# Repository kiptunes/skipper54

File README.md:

# tandem56
A partially-wired split keyboard that runs on one bluetooth-enabled microcontroller, one battery, and ZMK.

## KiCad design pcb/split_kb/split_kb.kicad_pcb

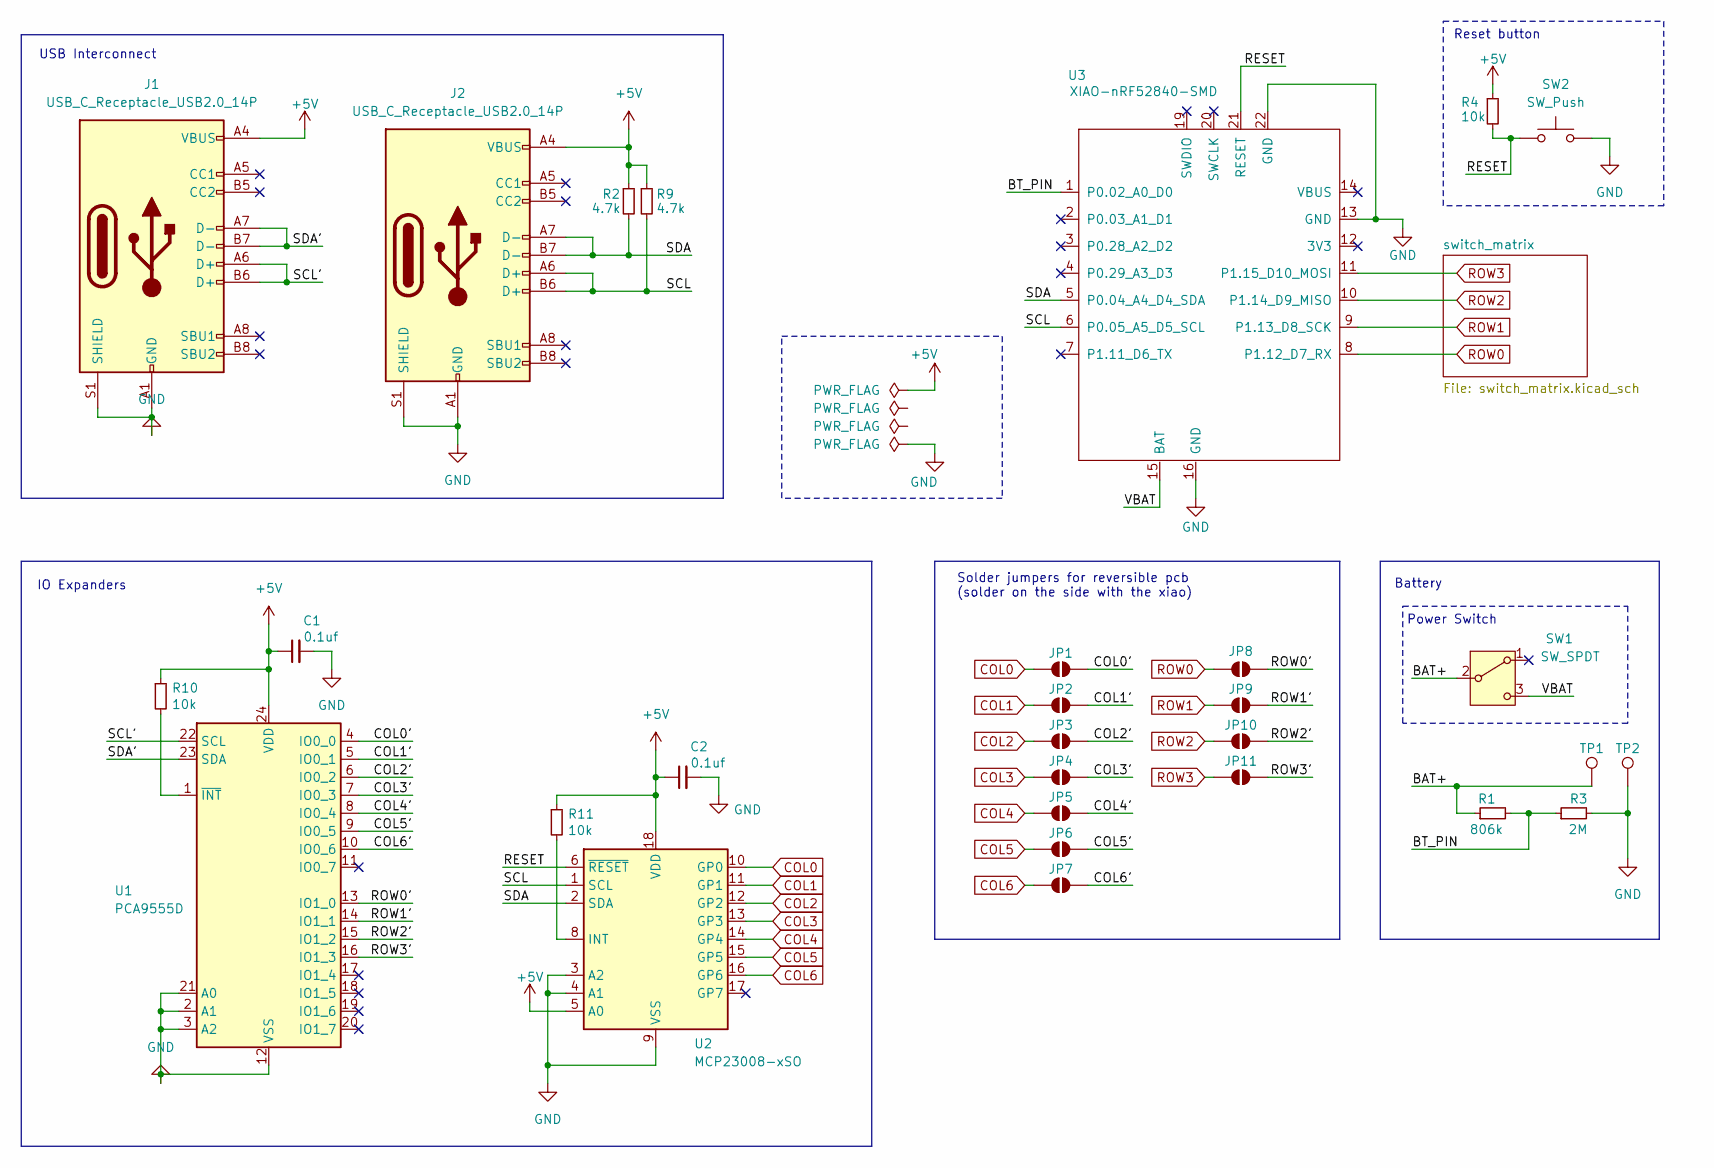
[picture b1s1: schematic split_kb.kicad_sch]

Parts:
C1, C2: 0.1uf; C_0805_2012Metric
J1, J2: USB_C_Receptacle_USB2.0_14P; USB_C_Receptacle_GCT_USB4105-xx-A_16P_TopMnt_Horizontal
JP1, JP2, JP3, JP4, JP5, JP6, JP7, JP8, JP9, JP10, JP11: SolderJumper_2_Open; SolderJumper-2_P1.3mm_Open_TrianglePad1.0x1.5mm
R1: 806k; R_0805_2012Metric
R2, R9: 4.7k; R_0805_2012Metric
R3: 2M; R_0805_2012Metric
R4, R10, R11: 10k; R_0805_2012Metric
SW1: SW_SPDT; SW_SPDT_CK_JS102011SAQN
SW2: SW_Push; SW_Tactile_SPST_Angled_PTS645Vx31-2LFS
TP1, TP2: TestPoint; TestPoint_Pad_D2.0mm
U1: PCA9555D; SSOP-24_5.3x8.2mm_P0.65mm
U2: MCP23008-xSO; SOIC-18W_7.5x11.6mm_P1.27mm
U3: XIAO-nRF52840-SMD; modified-XIAO-nRF52840-SMD

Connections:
+5V: C1.1, C2.1, J1.A4 (VBUS), J1.A9 (VBUS), J1.B4 (VBUS), J1.B9 (VBUS), J2.A4 (VBUS), J2.A9 (VBUS), J2.B4 (VBUS), J2.B9 (VBUS), R2.1, R4.1, R9.1, R10.1, R11.1, U1.24 (VDD), U2.5 (A0), U2.18 (VDD)
/BAT+: R1.1, SW1.2 (B), TP1.1
/BT_PIN: R1.2, R3.1, U3.1 (P0.02_A0_D0)
/COL0': JP1.1 (A), U1.4 (IO0_0)
/COL1': JP2.1 (A), U1.5 (IO0_1)
/COL2': JP3.1 (A), U1.6 (IO0_2)
/COL3': JP4.1 (A), U1.7 (IO0_3)
/COL4': JP5.1 (A), U1.8 (IO0_4)
/COL5': JP6.1 (A), U1.9 (IO0_5)
/COL6': JP7.1 (A), U1.10 (IO0_6)
/RESET: R4.2, SW2.1, U2.6 (~RESET), U3.21 (RESET)
/ROW0': JP8.1 (A), U1.13 (IO1_0)
/ROW1': JP9.1 (A), U1.14 (IO1_1)
/ROW2': JP10.1 (A), U1.15 (IO1_2)
/ROW3': JP11.1 (A), U1.16 (IO1_3)
/SCL: J2.A6 (D+), J2.B6 (D+), R9.2, U2.1 (SCL), U3.6 (P0.05_A5_D5_SCL)
/SCL': J1.A6 (D+), J1.B6 (D+), U1.22 (SCL)
/SDA: J2.A7 (D-), J2.B7 (D-), R2.2, U2.2 (SDA), U3.5 (P0.04_A4_D4_SDA)
/SDA': J1.A7 (D-), J1.B7 (D-), U1.23 (SDA)
/VBAT: SW1.3 (C), U3.15 (BAT)
COL0: JP1.2 (B), U2.10 (GP0); also elsewhere on the board
COL1: JP2.2 (B), U2.11 (GP1); also elsewhere on the board
COL2: JP3.2 (B), U2.12 (GP2); also elsewhere on the board
COL3: JP4.2 (B), U2.13 (GP3); also elsewhere on the board
COL4: JP5.2 (B), U2.14 (GP4); also elsewhere on the board
COL5: JP6.2 (B), U2.15 (GP5); also elsewhere on the board
COL6: JP7.2 (B), U2.16 (GP6); also elsewhere on the board
GND: C1.2, C2.2, J1.A1 (GND), J1.A12 (GND), J1.B1 (GND), J1.B12 (GND), J1.S1 (SHIELD), J2.A1 (GND), J2.A12 (GND), J2.B1 (GND), J2.B12 (GND), J2.S1 (SHIELD), R3.2, SW2.2, TP2.1, U1.2 (A1), U1.3 (A2), U1.12 (VSS), U1.21 (A0), U2.3 (A2), U2.4 (A1), U2.9 (VSS), U3.13 (GND), U3.16 (GND), U3.22 (GND)
unnamed: R10.2, U1.1 (~INT)
unnamed: R11.2, U2.8 (INT)
ROW0: JP8.2 (B), U3.8 (P1.12_D7_RX); also elsewhere on the board
ROW1: JP9.2 (B), U3.9 (P1.13_D8_SCK); also elsewhere on the board
ROW2: JP10.2 (B), U3.10 (P1.14_D9_MISO); also elsewhere on the board
ROW3: JP11.2 (B), U3.11 (P1.15_D10_MOSI); also elsewhere on the board

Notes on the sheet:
IO Expanders
Reset button
Power Switch
USB Interconnect
Solder jumpers for reversible pcb (solder on the side with the xiao)
Battery

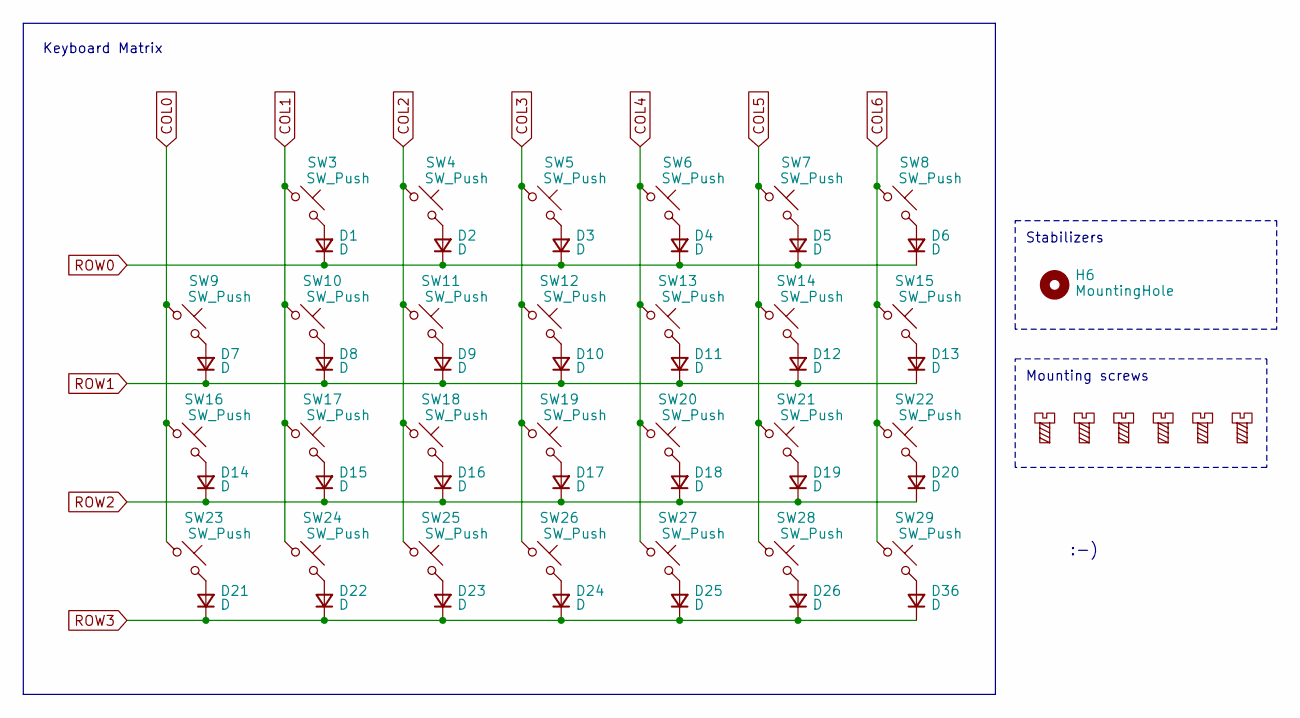
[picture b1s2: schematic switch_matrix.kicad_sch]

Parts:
D1, D2, D3, D4, D5, D6, D7, D8, D9, D10, D11, D12, D13, D14, D15, D16, D17, D18, D19, D20, D21, D22, D23, D24, D25, D26, D36: D; Diode-dual
H1, H2, H3, H4, H5, H7: MountingScrew; MountingHole_2.2mm_M2
H6: MountingHole; Choc-2u-cutout
SW3, SW4, SW5, SW6, SW7, SW8, SW9, SW10, SW11, SW12, SW13, SW14, SW15, SW16, SW17, SW18, SW19, SW20, SW21, SW22, SW23, SW24, SW25, SW26, SW27, SW28, SW29: SW_Push; Kailh_socket_PG1350_reversible

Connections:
COL0: SW9.1, SW16.1, SW23.1; also elsewhere on the board
COL1: SW3.1, SW10.1, SW17.1, SW24.1; also elsewhere on the board
COL2: SW4.1, SW11.1, SW18.1, SW25.1; also elsewhere on the board
COL3: SW5.1, SW12.1, SW19.1, SW26.1; also elsewhere on the board
COL4: SW6.1, SW13.1, SW20.1, SW27.1; also elsewhere on the board
COL5: SW7.1, SW14.1, SW21.1, SW28.1; also elsewhere on the board
COL6: SW8.1, SW15.1, SW22.1, SW29.1; also elsewhere on the board
unnamed: D1.2 (A), SW3.2
unnamed: D2.2 (A), SW4.2
unnamed: D3.2 (A), SW5.2
unnamed: D4.2 (A), SW6.2
unnamed: D5.2 (A), SW7.2
unnamed: D6.2 (A), SW8.2
unnamed: D7.2 (A), SW9.2
unnamed: D8.2 (A), SW10.2
unnamed: D9.2 (A), SW11.2
unnamed: D10.2 (A), SW12.2
unnamed: D11.2 (A), SW13.2
unnamed: D12.2 (A), SW14.2
unnamed: D13.2 (A), SW15.2
unnamed: D14.2 (A), SW16.2
unnamed: D15.2 (A), SW17.2
unnamed: D16.2 (A), SW18.2
unnamed: D17.2 (A), SW19.2
unnamed: D18.2 (A), SW20.2
unnamed: D19.2 (A), SW21.2
unnamed: D20.2 (A), SW22.2
unnamed: D21.2 (A), SW23.2
unnamed: D22.2 (A), SW24.2
unnamed: D23.2 (A), SW25.2
unnamed: D24.2 (A), SW26.2
unnamed: D25.2 (A), SW27.2
unnamed: D26.2 (A), SW28.2
unnamed: D36.2 (A), SW29.2
ROW0: D1.1 (K), D2.1 (K), D3.1 (K), D4.1 (K), D5.1 (K), D6.1 (K); also elsewhere on the board
ROW1: D7.1 (K), D8.1 (K), D9.1 (K), D10.1 (K), D11.1 (K), D12.1 (K), D13.1 (K); also elsewhere on the board
ROW2: D14.1 (K), D15.1 (K), D16.1 (K), D17.1 (K), D18.1 (K), D19.1 (K), D20.1 (K); also elsewhere on the board
ROW3: D21.1 (K), D22.1 (K), D23.1 (K), D24.1 (K), D25.1 (K), D26.1 (K), D36.1 (K); also elsewhere on the board

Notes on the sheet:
Mounting screws
Stabilizers
:-)
Keyboard Matrix

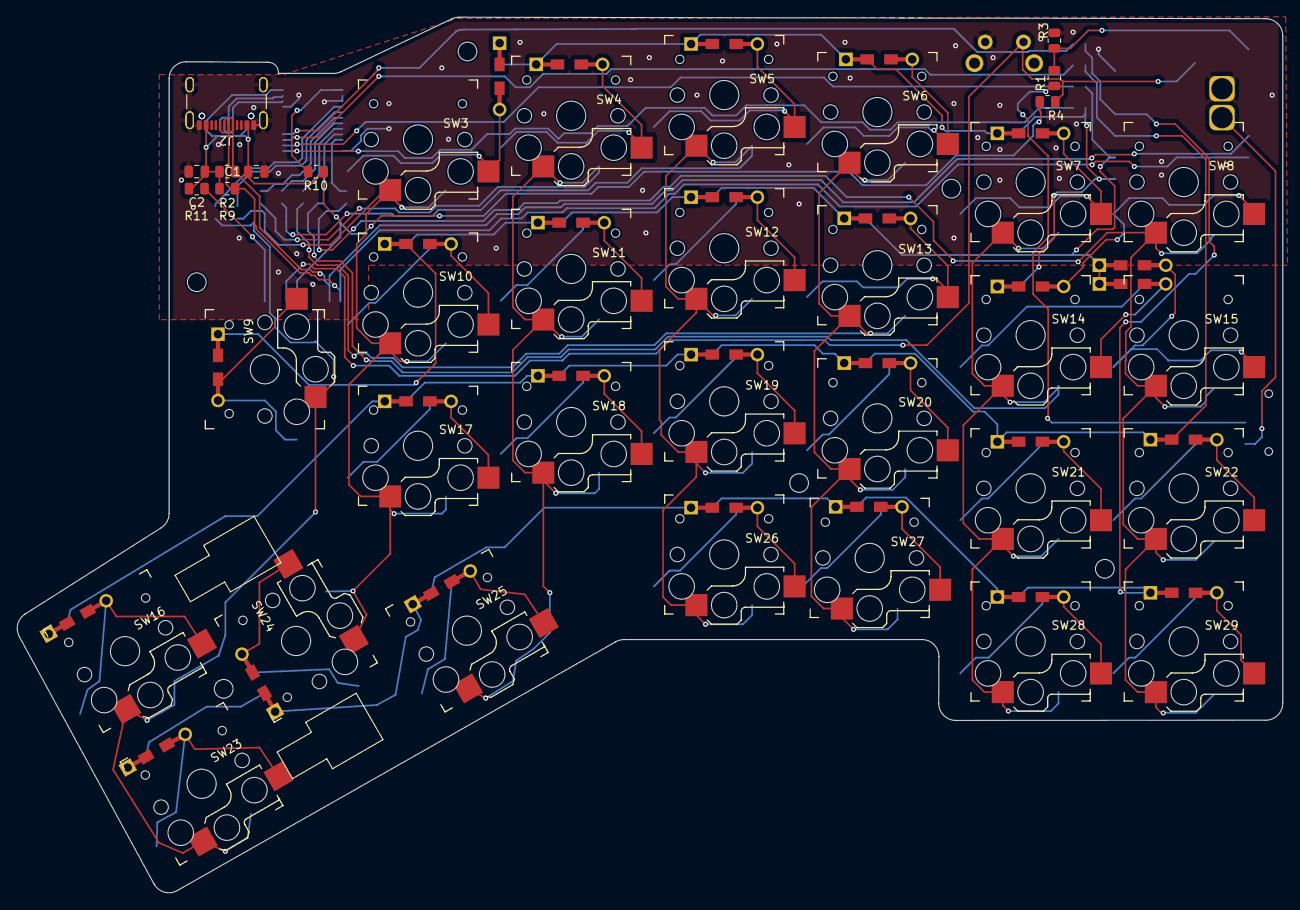
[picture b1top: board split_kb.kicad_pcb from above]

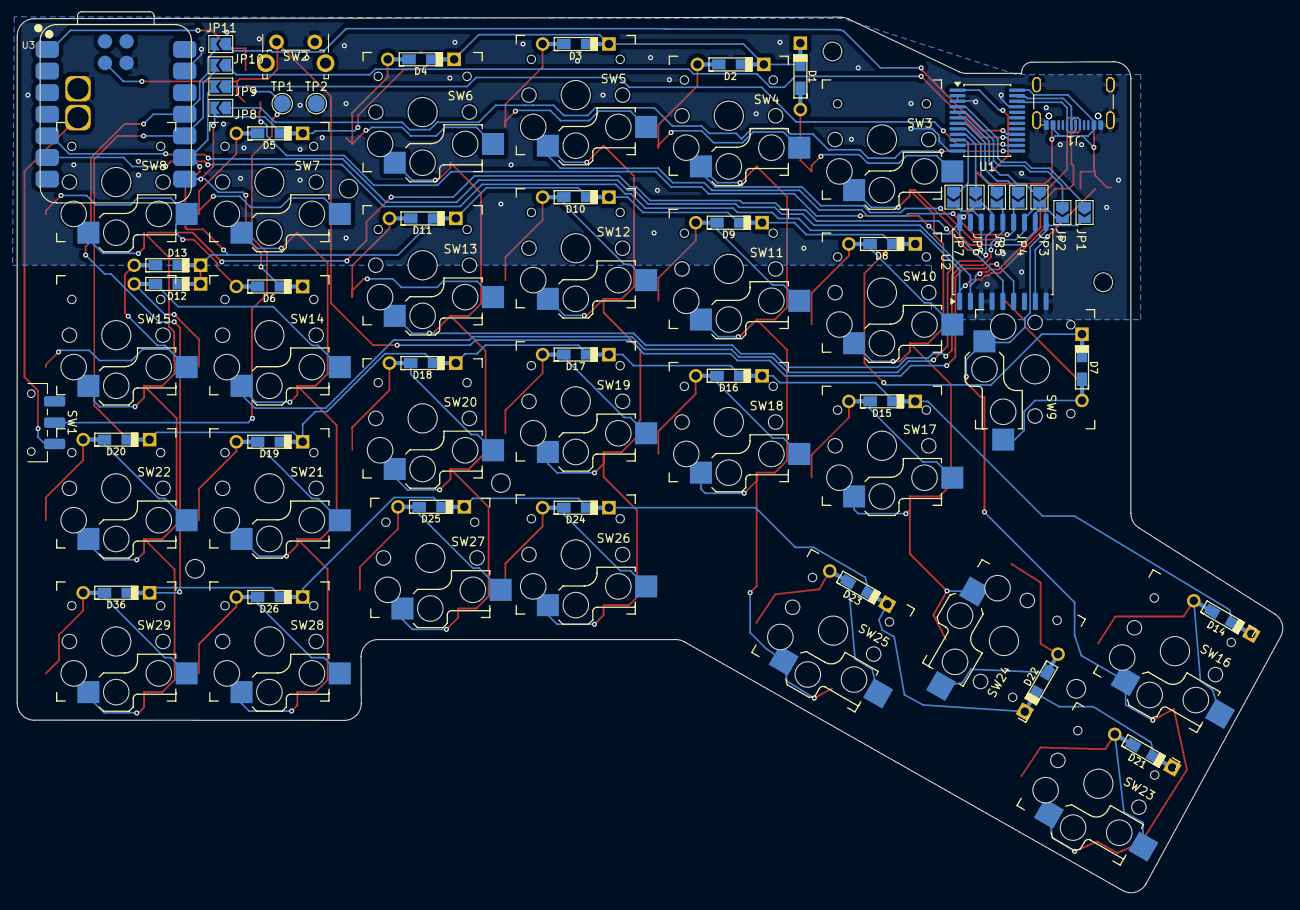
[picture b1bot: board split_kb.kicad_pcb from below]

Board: 2 copper layers, 148.7 x 102.9 mm, 90 parts (46 on the bottom side), 61 nets.

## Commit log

2026-03-02 Add license.
2026-03-02 Upload pcb v1
2026-03-06 rename
